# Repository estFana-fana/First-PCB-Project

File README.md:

# First-PCB-Project
This project is a handheld gaming console that can run snake game. The project is originally from this article: https://www.allaboutcircuits.com/projects/upgrading-my-retro-handheld-gaming-console-with-motion-control-and-an-lcd/
I have finished copying the schematic from the article above using Fusion 360 and 2D along with 3D design of the PCB design as well. 

Here are the image of the result:
The Schematic
![Schematic](
)
The 2D PCB design
![2D design](
)
The 3D PCB design
![3D design](
)
![Bottom](
)

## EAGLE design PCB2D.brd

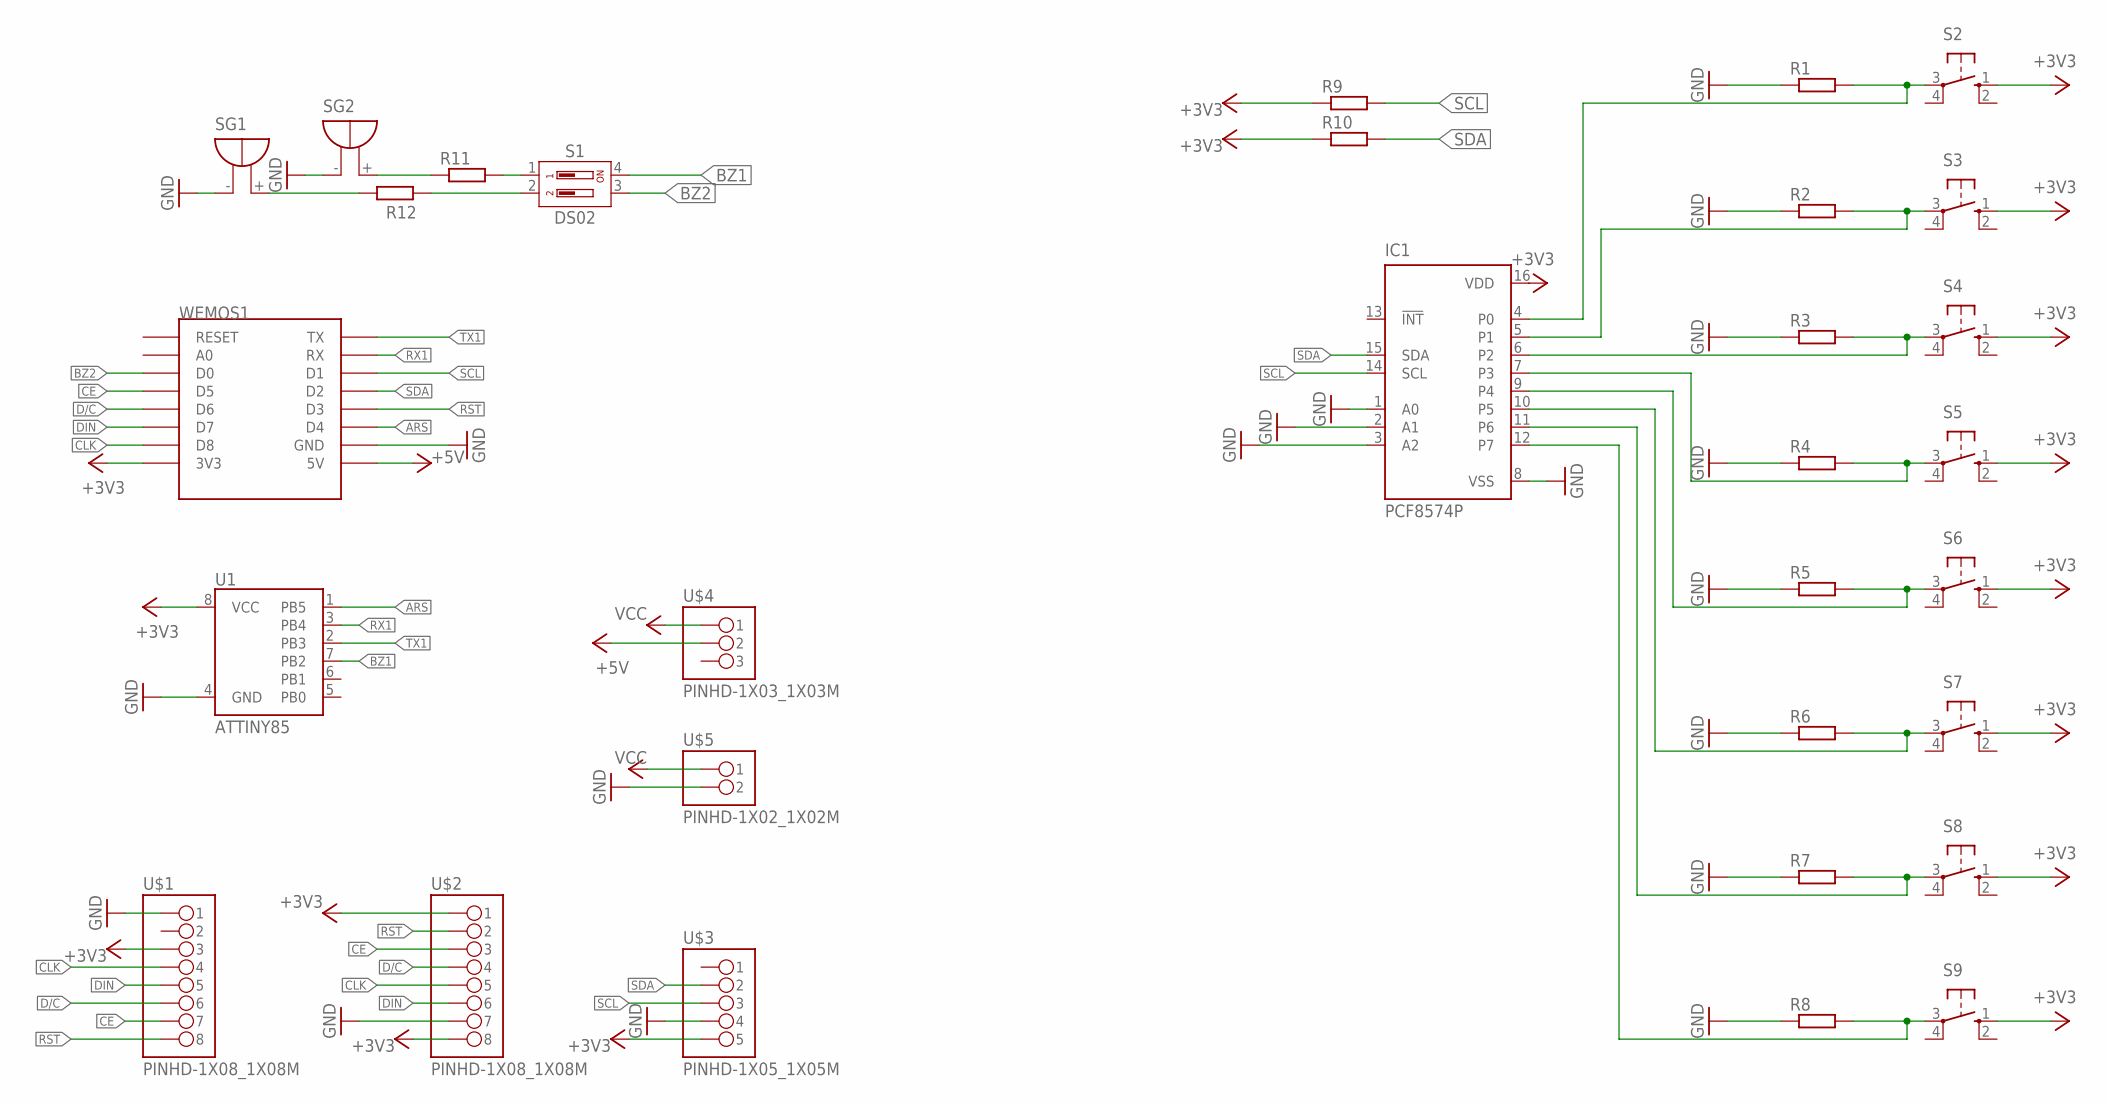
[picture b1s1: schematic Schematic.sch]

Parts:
IC1: PCF8574P; DIL16
R1, R2, R3, R4, R5, R6, R7, R8, R9, R10, R11, R12: R-EU_0207/10; 0207/10
S1: DS02; DS-02
S2, S3, S4, S5, S6, S7, S8, S9: 10-XX; B3F-10XX
SG1, SG2: F/QMBIII
U1: ATTINY85
U$1, U$2: PINHD-1X08_1X08M; 1X08
U$3: PINHD-1X05_1X05M; 1X05
U$4: PINHD-1X03_1X03M; 1X03
U$5: PINHD-1X02_1X02M; 1X02
WEMOS1: WEMOS-D1-MINI

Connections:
+3V3: IC1.16 (VDD), R9.1, R10.1, S2.1 (S), S3.1 (S), S4.1 (S), S5.1 (S), S6.1 (S), S7.1 (S), S8.1 (S), S9.1 (S), U1.8 (VCC), U$1.3, U$2.1, U$2.8, U$3.5, WEMOS1.3V3
+5V: U$4.2, WEMOS1.5V
ARS: U1.1 (PB5), WEMOS1.D4
BZ1: S1.4, U1.7 (PB2)
BZ2: S1.3, WEMOS1.D0
CE: U$1.7, U$2.3, WEMOS1.D5
CLK: U$1.4, U$2.5, WEMOS1.D8
D/C: U$1.6, U$2.4, WEMOS1.D6
DIN: U$1.5, U$2.6, WEMOS1.D7
GND: IC1.1 (A0), IC1.2 (A1), IC1.3 (A2), IC1.8 (VSS), R1.1, R2.1, R3.1, R4.1, R5.1, R6.1, R7.1, R8.1, SG1.- (+), SG2.- (+), U1.4 (GND), U$1.1, U$2.7, U$3.4, U$5.2, WEMOS1.GND
unnamed: R11.2, S1.1
unnamed: R12.2, S1.2
unnamed: R11.1, SG2.+ (-)
unnamed: R12.1, SG1.+ (-)
unnamed: IC1.4 (P0), R1.2, S2.3
unnamed: IC1.5 (P1), R2.2, S3.3
unnamed: IC1.6 (P2), R3.2, S4.3
unnamed: IC1.7 (P3), R4.2, S5.3
unnamed: IC1.9 (P4), R5.2, S6.3
unnamed: IC1.10 (P5), R6.2, S7.3
unnamed: IC1.11 (P6), R7.2, S8.3
unnamed: IC1.12 (P7), R8.2, S9.3
RST: U$1.8, U$2.2, WEMOS1.D3
RX1: U1.3 (PB4), WEMOS1.RX
SCL: IC1.14 (SCL), R9.2, U$3.3, WEMOS1.D1
SDA: IC1.15 (SDA), R10.2, U$3.2, WEMOS1.D2
TX1: U1.2 (PB3), WEMOS1.TX
VCC: U$4.1, U$5.1

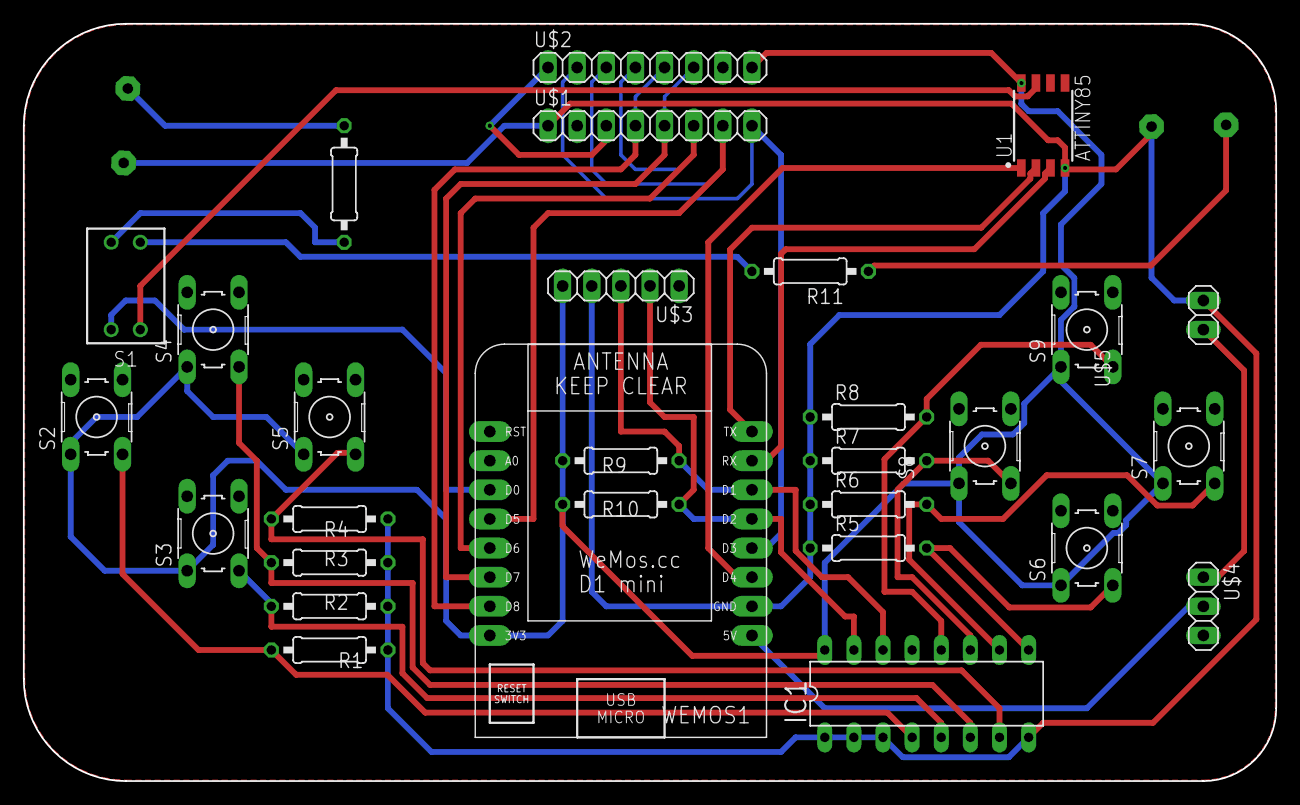
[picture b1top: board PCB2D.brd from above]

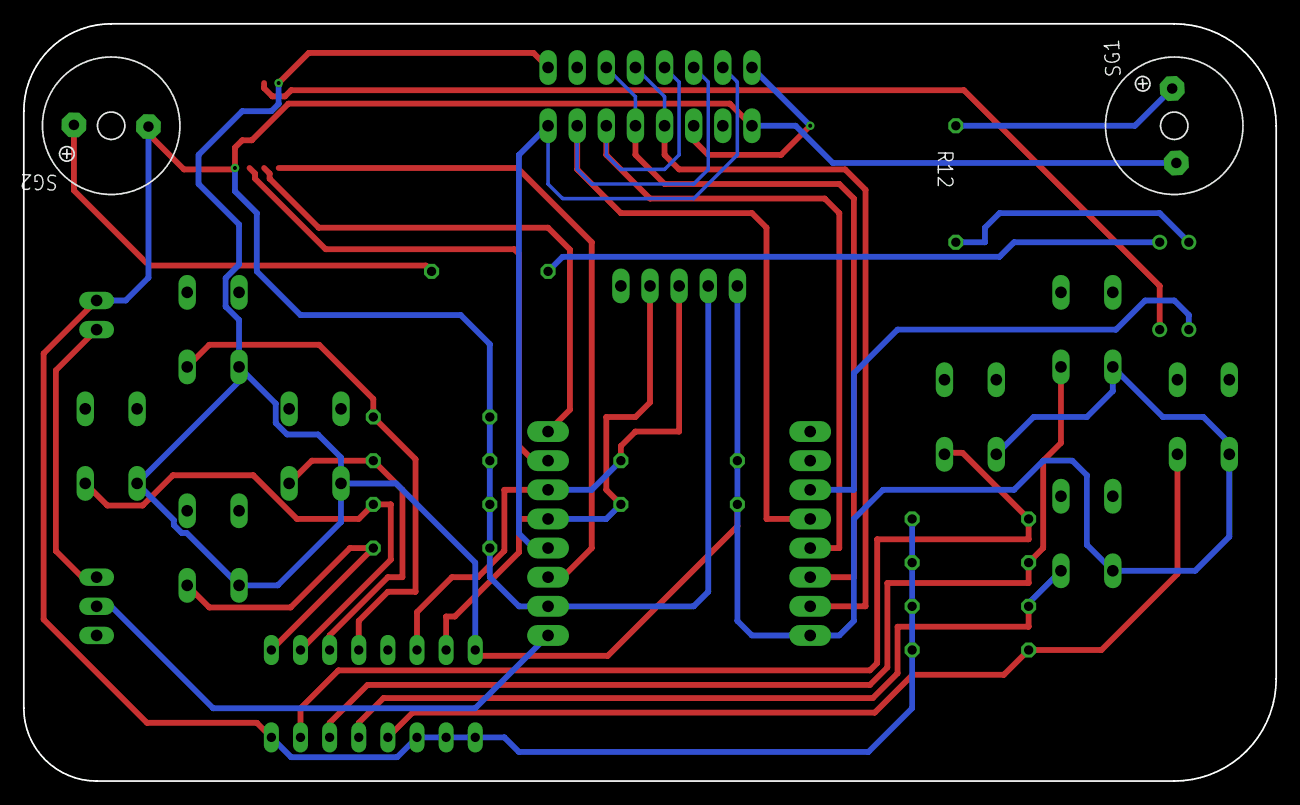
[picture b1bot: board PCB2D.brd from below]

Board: 2 copper layers, 109.2 x 66.0 mm, 31 parts (2 on the bottom side), 28 nets.

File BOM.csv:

Reference Designators;Quantity;Description;Package;Value;Manufacturer;Manufacturer Part Number;Vendor;Vendor Part Number;Top/Bottom;
;1;Board;Board;;;;;;;
IC1;1;I2C-Bus Remote 8-bit I/O expander;DIL16;PCF8574P;;PCF8574PN;;;Top;
R1, R2, R3, R4, R5, R6, R7, R8, R9, R10, R11, R12;12;RESISTOR, European symbol;0207/10;;;;;;Top;
S1;1;DIL/CODE Switch;DS-02;DS02;Multicomp Pro;MCNDS-02V;;;Top;
S2, S3, S4, S5, S6, S7, S8, S9;8;OMRON SWITCH;B3F-10XX;;;B3F-1000;;;Top;
SG1, SG2;2;BUZZER Source: Buerklin;F/QMBIII;F/QMBIII;;;;;Bottom;
U$1, U$2;2;;1X08;PINHD-1X08_1X08M;;;;;Top;
U$3;1;;1X05;PINHD-1X05_1X05M;;;;;Top;
U$4;1;;1X03;PINHD-1X03_1X03M;;;;;Top;
U$5;1;;1X02;PINHD-1X02_1X02M;;;;;Top;
U1;1;;ATTINY85;ATTINY85;;;;;Top;
WEMOS1;1;WeMos.cc;WEMOS-D1-MINI;;;;;;Top;

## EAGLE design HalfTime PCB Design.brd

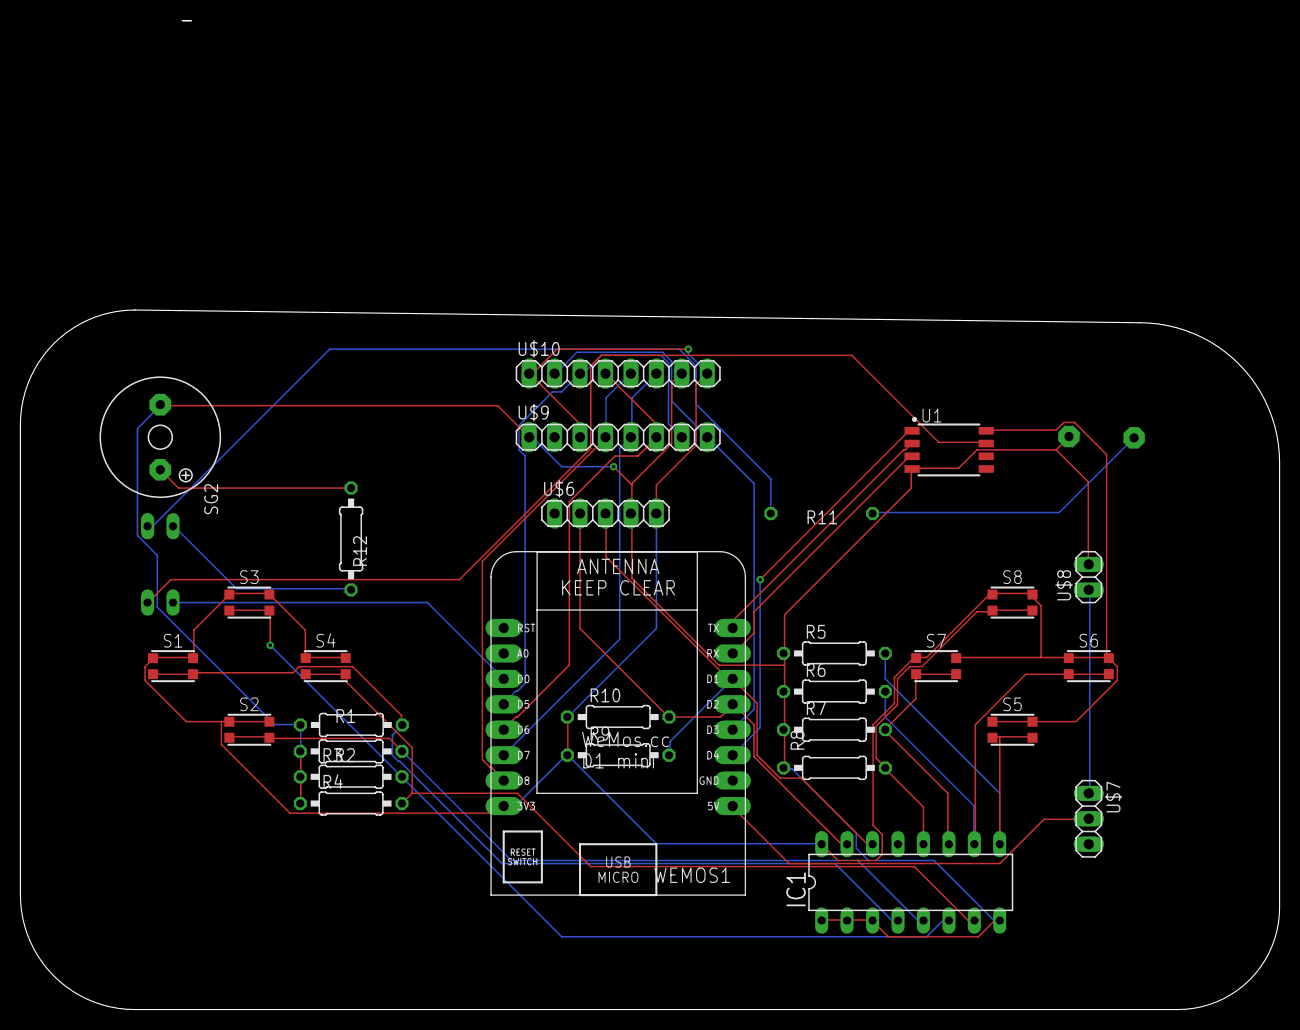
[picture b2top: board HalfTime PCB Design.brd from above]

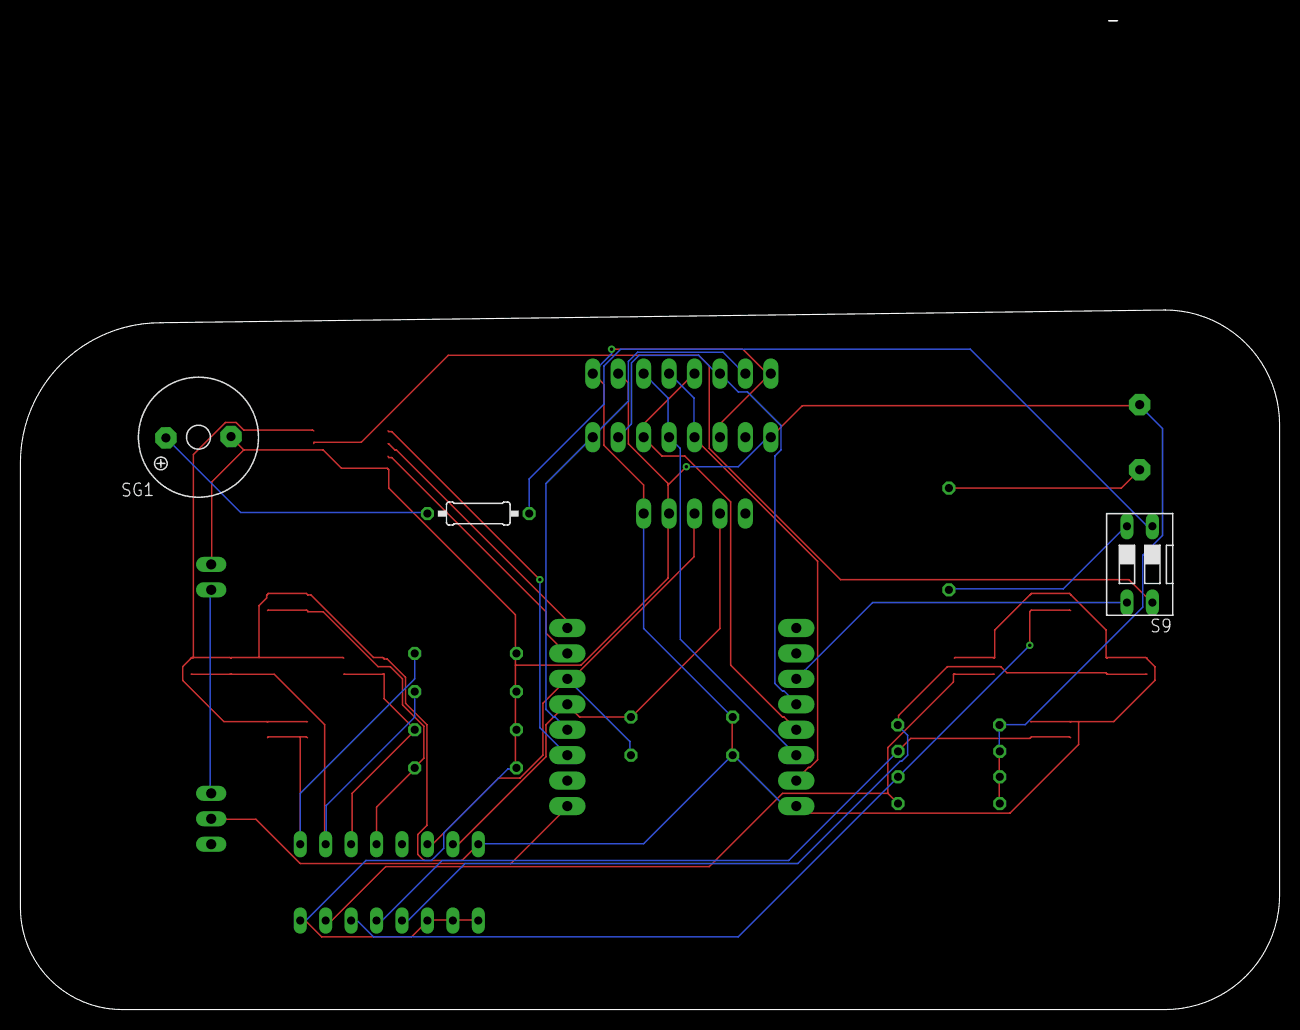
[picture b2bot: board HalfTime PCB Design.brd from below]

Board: 2 copper layers, 125.7 x 69.9 mm, 31 parts (3 on the bottom side), 28 nets.

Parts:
IC1: PCF8574P; DIL16
R1, R2, R3, R4, R5, R6, R7, R8, R9, R10, R11, R12: 0207/10
S1, S2, S3, S4, S5, S6, S7, S8: SPST-NO_SWITCH_KMR2; KMR2
S9: DS-02
SG1, SG2: F/QMBIII
U1: ATTINY85
U$6: PINHD-1X05_1X05M; 1X05
U$7: PINHD-1X03_1X03M; 1X03
U$8: PINHD-1X02_1X02M; 1X02
U$9, U$10: PINHD-1X08_1X08M; 1X08
WEMOS1: WEMOS-D1-MINI

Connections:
+3V3: IC1.16, R9.1, R10.1, S1.1, S1.4, S2.1, S2.4, S3.1, S3.4, S4.1, S4.4, S5.1, S5.4, S6.1, S6.4, S7.1, S7.4, S8.1, S8.4, U1.8, U$6.5, U$9.3, U$10.1, U$10.8, WEMOS1.3V3
+5V: U$7.2, WEMOS1.5V
ARS: U1.1, WEMOS1.D4
BZ1: S9.4, U1.7
BZ2: S9.3, WEMOS1.D0
CE: U$9.7, U$10.3, WEMOS1.D5
CLK: U$9.4, U$10.5, WEMOS1.D8
D/C: U$9.6, U$10.4, WEMOS1.D6
DIN: U$9.5, U$10.6, WEMOS1.D7
GND: IC1.1, IC1.2, IC1.3, IC1.8, R1.1, R2.1, R3.1, R4.1, R5.1, R6.1, R7.1, R8.1, SG1.-, SG2.-, U1.4, U$6.4, U$8.2, U$9.1, U$10.7
unnamed: R12.1, SG2.+
unnamed: R12.2, S9.2
unnamed: R11.1, SG1.+
unnamed: R11.2, S9.1
unnamed: IC1.4, R1.2, S1.2, S1.3
unnamed: IC1.6, R3.2, S3.2, S3.3
unnamed: IC1.5, R2.2, S2.2, S2.3
unnamed: IC1.7, R4.2, S4.2, S4.3
unnamed: IC1.9, R5.2, S5.2, S5.3
unnamed: IC1.10, R6.2, S6.2, S6.3
unnamed: IC1.11, R7.2, S7.2, S7.3
unnamed: IC1.12, R8.2, S8.2, S8.3
RST: U$9.8, U$10.2, WEMOS1.D3
RX1: U1.3, WEMOS1.RX
SCL: IC1.14, R9.2, U$6.3, WEMOS1.D1
SDA: IC1.15, R10.2, U$6.2, WEMOS1.D2
TX1: U1.2, WEMOS1.TX
VCC: U$7.1, U$8.1

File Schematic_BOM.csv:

Reference Designators;Quantity;Description;Package;Value;Manufacturer;Manufacturer Part Number;Vendor;Vendor Part Number;Top/Bottom;
;1;Board;Board;;;;;;;
IC1;1;I2C-Bus Remote 8-bit I/O expander;DIL16;PCF8574P;;PCF8574PN;;;Top;
R1, R2, R3, R4, R5, R6, R7, R8, R9, R10, R11, R12;12;RESISTOR, European symbol;0207/10;;;;;;-;
S1, S2, S3, S4, S5, S6, S7, S8;8;SPST Switches with NO Configuration;KMR2;SPST-NO_SWITCH_KMR2;C&K;KMR211G LFS;;;Top;
S9;1;DIL/CODE SWITCH;DS-02;;;;;;Bottom;
SG1, SG2;2;BUZZER Source: Buerklin;F/QMBIII;F/QMBIII;;;;;-;
U$6;1;;1X05;PINHD-1X05_1X05M;;;;;Top;
U$7;1;;1X03;PINHD-1X03_1X03M;;;;;Top;
U$8;1;;1X02;PINHD-1X02_1X02M;;;;;Top;
U$9, U$10;2;;1X08;PINHD-1X08_1X08M;;;;;Top;
U1;1;;ATTINY85;ATTINY85;;;;;Top;
WEMOS1;1;WeMos.cc;WEMOS-D1-MINI;;;;;;Top;

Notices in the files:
parts and their libraries:
SparkFun-IC-Microcontroller: Licensing: Creative Commons ShareAlike 4.0 International - https://creativecommons.org/licenses/by-sa/4.0
